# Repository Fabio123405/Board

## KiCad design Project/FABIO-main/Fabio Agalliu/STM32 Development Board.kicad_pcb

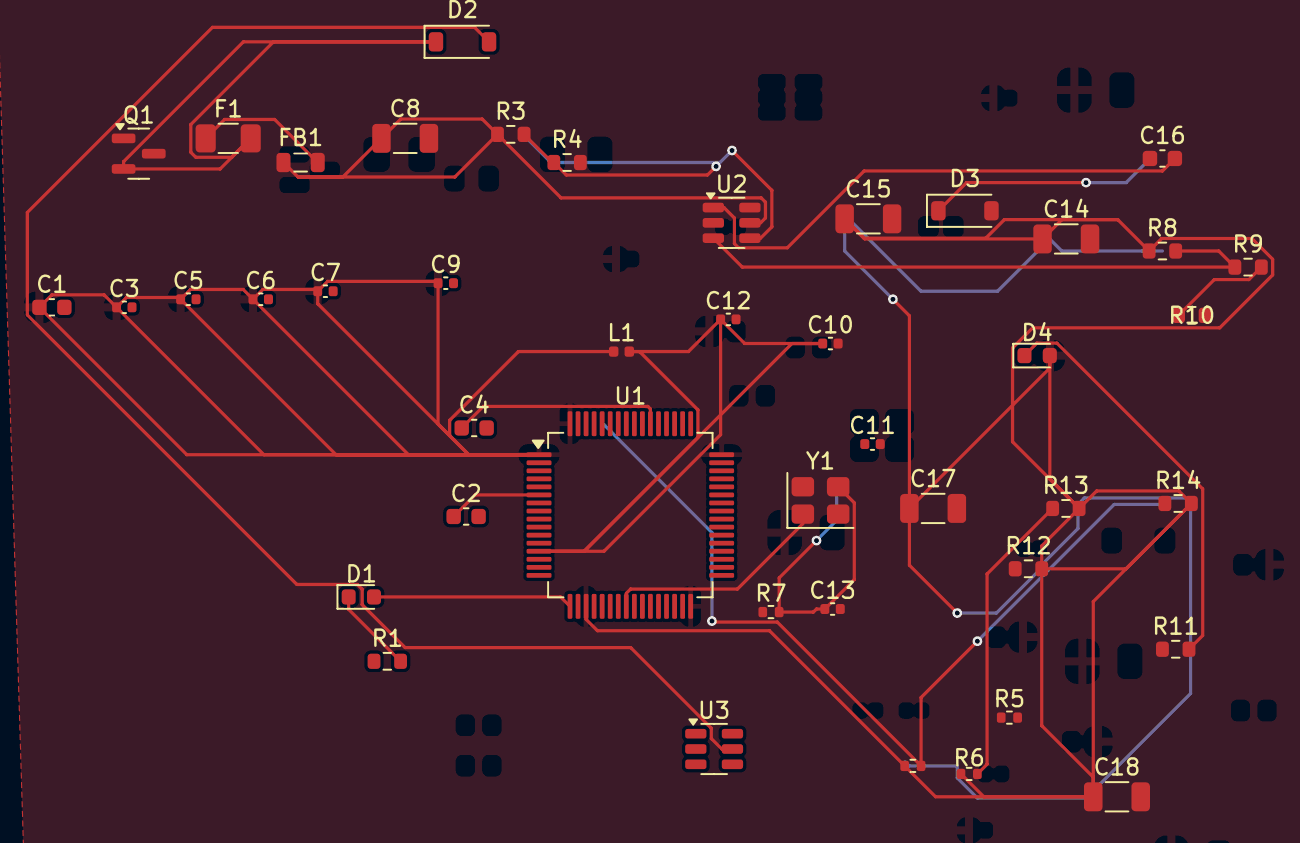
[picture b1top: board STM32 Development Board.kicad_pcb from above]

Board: 4 copper layers, 44 parts (0 on the bottom side), 23 nets.

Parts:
C1: 4u7; C_0603_1608Metric
C2, C4: 2u2; C_0603_1608Metric
C3, C5, C6, C7, C9: 100n; C_0402_1005Metric
C8, C14, C15: 10u; C_1206_3216Metric
C10: 1u; C_0402_1005Metric
C11, C13: 12p; C_0402_1005Metric
C12: 10n; C_0402_1005Metric
C16: 10n; C_0603_1608Metric
C17: 100n; C_1206_3216Metric
C18: 4u7; C_1206_3216Metric
D1: BLUE; LED_0603_1608Metric
D2, D3: B5819W; D_SOD-123
D4: RED; LED_0603_1608Metric
F1: 250mA; Fuse_1206_3216Metric
FB1: 600 @ 600MHz; L_0805_2012Metric
L1: 39n; L_0402_1005Metric
Q1: AO3401A; SOT-23
R1: 1k5; R_0603_1608Metric
R2, R6: 2k2; R_0402_1005Metric
R3: 100k; R_0603_1608Metric
R4: 68k; R_0603_1608Metric
R5: 10k; R_0402_1005Metric
R7: 47; R_0402_1005Metric
R8: 47k; R_0603_1608Metric
R9: 15k; R_0603_1608Metric
R10: 270; R_0603_1608Metric
R11: 1k; R_0603_1608Metric
R12, R13, R14: 2k2; R_0603_1608Metric
U1: STM32F405RGT6; LQFP-64_10x10mm_P0.5mm
U2: MP2359DJ-LF-Z; SOT-23-6
U3: USBLC6-2SC6; SOT-23-6
Y1: 16MHz; Crystal_SMD_3225-4Pin_3.2x2.5mm

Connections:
+3.3V: C1.1, C3.1, C5.1, C6.1, C7.1, C9.1, C14.1, C15.1, C17.1, C18.1, D4.2 (A), L1.1, R2.1, R6.1, R8.1, R12.2, R13.2, R14.2, U1.1 (VBAT), U1.19 (VDD), U1.32 (VDD), U1.48 (VDD), U1.64 (VDD)
+3.3VA: C10.1, C12.1, L1.2, U1.13 (VDDA)
+5V: D2.2 (A), U3.5 (VBUS)
BOOT0: R5.2, U1.60 (BOOT0)
BUCK_BST: C16.2, U2.1 (BST)
BUCK_EN: R3.2, R4.1, U2.4 (EN)
BUCK_FB: R8.2, R9.1, U2.3 (FB)
BUCK_IN: C8.1, FB1.1, R3.1, U2.5 (IN)
BUCK_SW: C16.1, D3.1 (K), U2.6 (SW)
GND: C1.2, C2.2, C3.2, C4.2, C5.2, C6.2, C7.2, C8.2, C9.2, C10.2, C11.2, C12.2, C13.2, C14.2, C15.2, C17.2, C18.2, D3.2 (A), Q1.1 (G), R1.1, R4.2, R10.2, R11.1, U1.12 (VSSA), U1.18 (VSS), U1.63 (VSS), U2.2 (GND), U3.2 (GND), Y1.2, Y1.4
HSE_IN: C11.1, U1.24 (PC4), Y1.1
HSE_OUT: R7.1, U1.25 (PC5)
I2C1_SCL: R2.2, R14.1, U1.59 (PB7)
I2C1_SDA: R6.2, R13.1, U1.61 (PB8)
LED_STATUS: D1.2 (A), U1.17 (PA3)
unnamed: C13.1, R7.2, Y1.3
unnamed: D1.1 (K), R1.2
unnamed: D2.1 (K), F1.2, Q1.2 (S)
unnamed: D4.1 (K), R11.2
unnamed: F1.1, FB1.2
unnamed: R9.2, R10.1
unnamed: C4.1, U1.54 (PD2)
unnamed: C2.1, U1.6 (PH1)

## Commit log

2025-06-13 temp
2025-06-13 Create temp
